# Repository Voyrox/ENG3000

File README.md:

# ENGG3000 Group 1

ESP32 ultrasonic sensor nodes that detect boats and report readings to a web dashboard.

## Architecture

```
ESP32 ── Wi-Fi ──▶ gateway/server ── TCP :3000 ──▶ Python Server
                                      └── WebSocket:8765 ──▶ Browser
                                    │
                                    └── REST:5000 ──▶ /api/nodes
```

### ESP32 → Server (TCP)

Each ESP32 is a servo scanner (`src/Scanner.cpp`; every pin and setting is in `src/Config.h`): two ultrasonic sensors side by side (left: echo/trigger on GPIO 13/12, right: GPIO 27/26) on a servo (GPIO 33) that turns towards whichever sensor sees the player, plus the dead-zone buzzer (GPIO 32). Every signal is on the board's VIN-to-EN header; the sensors' 3V3 is on the other one. Nodes scan one at a time: the server hands out turns (`TURN` / `HALT`) so their pings never overlap. It connects to the laptop hotspot, opens a persistent TCP socket on port `3000`, receives a numeric node ID, and sends a JSON line after every scan step:

```json
{"nodeId":1,"mac":"14:08:08:AB:F6:20","avg":82.40,"left":81.90,"right":82.90,"angle":112,"scanState":0}
```

- `avg` is the node's distance to the player (cm): the mean of the ultrasonics reading inside the scan range, or the nearer real echo if neither is; `-1` when neither heard anything
- `left` / `right` are the two ultrasonics (cm), `-1` for no echo
- `angle` is the servo angle the pair was read at: 90 points straight out into the play area, larger turns towards screen-left
- `scanState` is `0` found (both readings agree), `1` half-found (one sees the player), `2` lost (sweeping)

The server sends control lines back: `SYNC <tick>`, `TURN` / `HALT`, `ROLE LEFT` / `ROLE RIGHT` once the game's calibration screen has identified the node (again whenever it reconnects), which sets that mount's servo limits, and `AIM 90` / `SCAN` while the calibration screen is open / after it closes, `PULSES <n>` (multi-pulse, below), `LOOK <deg>` (handover, below), and `FARHOLD <0|1>` / `FARSTEER <0|1>` (far hold and far steer, below). A node boots holding its servo at 90 and sweeps only once told `SCAN`; the server sends `AIM 90` or `SCAN` the moment a node connects, so one that reboots mid-calibration never moves.

**Multi-pulse** is the `PULSES <n>` command: in found or half-found, the node takes `n` pulse pairs at one angle (1 = off, the default; at most 5), averages each sensor's readings with outliers left out, and only then reports one reading and moves. A lost pair still sweeps straight away. "Outliers" means: pulses with no echo are skipped, echoes outside the play area are skipped if any pulse saw the player inside it, then an echo more than `OUTLIER_TOLERANCE_CM` (20 cm) from the median is dropped (for two echoes that disagree, the nearer one is kept), and the rest are averaged. It is switched with the **Pulses** button on the game screen (top right: Off, 2, 3), which sends `{"type": "nodes:pulses", "count": 3}`; the server passes the count on to every node, and again to each node as it connects. With multi-pulse on, a node reports about once every `n` pairs while it has the player, instead of after every pair.

**Far hold and far steer** are two server → node lines, `FARHOLD <0|1>` and `FARSTEER <0|1>` (`src/CommandHandler.cpp`): `1` turns the setting on, `0` off. Far hold: after an echo at least `FAR_RANGE_CM` (100 cm) out, a lost pair keeps the servo where it is, for up to `FAR_HOLD_PAIRS` (3) lost pairs in a row, before the sweep starts. Far steer: a half-found echo that far out steers by `FAR_STEER_STEP_DEG` (1 degree) instead of `STEER_STEP_DEG` (3). Both are on in the firmware until the server says otherwise (`DEFAULT_FAR_HOLD`, `DEFAULT_FAR_STEER` in `src/Config.h`) and on in the server (`nodes_far` in `app.py`), which sends both lines to every node as it connects, and the changed one to every connected node when a switch changes:

```text
FARHOLD 1
FARSTEER 0
```

They are switched with **Far hold** and **Far steer** on the phone control panel (`/control`, `CON=1`, under *Sensors*). Those buttons go straight to the server, so they work with no game page open; `enabled` (boolean) is the new setting, and anything that is not `true` or `false` is ignored:

```json
{"action": "farHold",  "enabled": false}
{"action": "farSteer", "enabled": true}
```

The server answers every control panel with `far:status` (server → control panel), and sends it to each panel as it connects; `hold` and `steer` (booleans) are the two settings as the server holds them, and the panel's buttons show them:

```json
{"type": "far:status", "hold": true, "steer": false}
```

**Handover** (`Website/handover.py`): when one node has seen the player in one place for 5 s, the server aims the other node at them. A node's confidence is the share of its readings in the last 5 s that land inside the play area within 20 cm of their median point; dropped echoes count against it. It is confident at 80% or more, once it has been reporting for 5 s. While one node is confident and the other is not seeing the player there, the server sends the other `LOOK <deg>`, the bearing from it to that point. It is only ever sent while that node does not hold the turn, and is sent again whenever the bearing moves by more than 5 degrees, until the node's own reading agrees (within 30 cm). `LOOK` is not a hold: the node turns there and tracks, steers and sweeps from that angle as usual, after waiting out the swing (`LOOK_SETTLE_MS_PER_DEG`). Every node's confidence, the ± spread of its points and which node it is following go out in `nodes:update` as `confidence`, and the phone control panel shows them in its Sensors table. `HANDOVER=0 python Website/app.py` keeps the confidence but sends no `LOOK`; the control panel's Handover switch (Sensors) does the same while the server runs, and the server tells the panel which it is (`handover:status`). With the empty-room firmware, a node learning the room is never aimed, and one whose room is not learnt yet never counts as confident, because a chair is the steadiest "player" there is.

**Search** (`Website/search.py`, Aaron, 6 Oct): a node that loses the player is first aimed back at the cell they most likely are in, and only sweeps once it has checked there. For a still player the cell is the one both nodes' found and half-found readings put them in most often over the 3 s before the latest of them (each reading's own point: its distance plus the body radius along its servo angle; ties go to the latest); for a moving one, the cell they were walking into (`heading.py`, from the game's `track:update`, when its Tracking detector says they are moving; the Heading switch turns this off). From the node's first lost reading the server sends it `LOOK <deg>`, the bearing to the cell's centre within its servo's limits, and sends it again after each lost reading there, since the firmware sweeps a step after every lost reading; after 3 lost readings at the cell it sends nothing more and the sweep takes over. A found or half-found reading ends it. A node that has given up on a cell only looks again for someone seen after it gave up (Aaron: "after some time it should just give up if not found"); a cell needs 2 readings in the window, so one stray echo never sends it back. After a far echo (100 cm or more, Far hold on) the firmware's far hold goes first and the search starts on the last held reading. With no reading on the board in the last 5 s there is no cell, and a lost node sweeps as before. The search's `LOOK` goes before the handover's, which leaves a node being searched alone. Each node's search goes out in `nodes:update` as `search` (the State column on the control panel says "checking" and the cell, then "sweeping"). `SEARCH=0 python Website/app.py` starts with it off; the control panel's Search switch (Sensors) turns it off and on while the server runs (`search:status`). It needs no new firmware. The game resets it with `round:start` (which restarts the server-side chain too), and `calibration:update` gives it the cells' depths.

#### Firmware layout (`src/`)

| File | What it is |
|------|------------|
| `Config.h` | Every pin, range, timing, step size, servo limit, network setting and multi-pulse setting |
| `main.cpp` | Creates the objects below; `setup()` and `loop()` |
| `UltrasonicSensor.h/.cpp` | `UltrasonicSensor`: one sensor, a distance in cm or `-1` for no echo |
| `ScannerServo.h/.cpp` | `ScannerServo`: the servo angle, per-role limits (`NodeRole`), the calibration hold and settle time |
| `Scanner.h/.cpp` | `Scanner`: the found / half-found / lost state machine and multi-pulse; `ScanReading`, `ScanState` |
| `NodeConnection.h/.cpp` | `NodeConnection`: Wi-Fi, the TCP socket, the handshake and node id, sending and reading lines |
| `ServerDiscovery.h/.cpp` | Finds the server on the local subnet (only with `AUTO_DISCOVER_SERVER`) |
| `CommandHandler.h/.cpp` | `CommandHandler`: carries out the server's control lines |
| `Telemetry.h/.cpp` | The JSON line above |

The Wi-Fi network and server IP default to the values in `Config.h`. To use your own without committing them, add them to your own (gitignored) `platformio.ini`:

```ini
build_flags =
    '-DNODE_WIFI_SSID="MyHotspot"'
    '-DNODE_WIFI_PASSWORD="secret"'
    '-DNODE_SERVER_IP="192.168.137.1"'
```

**Calibration** is the game's sensor-assignment screen: both servos are held still at 90 degrees (`AIM 90`) for the whole screen - through both steps, LEFT then RIGHT - while the operator aims the nodes straight out into the play area by hand and identifies each node with a hand in front of it; each live-readings row shows the angle the node reports, amber if it is not 90; Start Game then lets the nodes scan again (`SCAN`). There is no play-area (corner) calibration: the game plays on the default bounds, rows between 20 and 140 cm in every column. Each game page asks for the hold with `{"type": "nodes:aim", "hold": true}` and releases it with `false`; the servos stay held while any open page is on the calibration screen, so another tab or device on a different screen cannot release them, and a page that closes stops holding.

The game puts each node on the screen edge at the centre of an outer column. How the player is placed is switched on the phone's `/control` page only (Aaron, 5 Oct; the game board draws one cursor and no buttons): **Dynamic** (the default), **Line of sight**, **Trilateration** or **Average**, under *Placing the player*. Picking one of the last three turns Dynamic off. With Dynamic on, its button says which one it is following (e.g. `Dynamic (TRI)`), or which of its rules is placing the player: `FAR` (far priority: both nodes read past 110 cm and agree), `A1` / `A3` (the near node in its far corner), `MID`, `COL L` / `COL R` (the column lock: where the two servo lines cross) or `L` / `R` (a lone confident node); each rule has its own switch under *Dynamic's rules*. **Compare**, beside it, rings where line of sight, trilateration and the average put the player (LOS, TRI, AVG) on the control panel's pad, while the cyan cursor follows the one placing the player (the thick ring). The game's sensor panel lists all three positions. See *Placing the player* under the filtering pipeline. With no `angle` from either node there is no line of sight, and every method is trilateration.

**Out of bounds** appears in one case only: both nodes are lost (Aaron, 5 Oct). Each node's last *n* readings are scored as the control panel shows them - *found* +1, *half* 0, *lost* -1 - and a node whose scores add up to 0 or less is lost, so the odd found reading among lost ones does not stop it, and a node mostly finding the player never is. *n* is 21 by default; set it on the phone control panel under *Out of bounds* (minus and plus), which also shows each node's score now. The game keeps it in that browser, and passes it to the server when `SERVER_FILTERING` is on. Each reading counts once, when it arrives; a node waiting for its turn keeps the readings of its last one, and a node is not lost until it has had *n* readings in the round. A position off the board keeps the player on the edge square, a tenth of a square inside the edge (`EDGE_INSET`), and the game carries on; the sensor panel says `off board: edge`. Unusable readings are ridden out on the last square for as long as they last. If neither node sends anything for 5 s (`tuneSensor({ offlineMs })`), or the server says both are offline, the game says **Sensors offline** instead and the round waits. Waiting for a first position shows no message.

The board is drawn with the row **nearest the screen at the top**, so stepping towards the screen moves the cursor up. Only the drawing is flipped (`boardRow()` in `game.js`, one switch, `NEAR_ROW_AT_TOP`): grid row `gy = 0` is still the row nearest the screen everywhere else, and left/right is unchanged. The phone control panel's touchpad maps onto the board as drawn. A finger on it takes the game's cursor over from whichever mode is running (sensors or mouse) and lifting it hands the cursor straight back; nothing else on the game screen changes (Aaron, 5 Oct). The sensors keep running underneath - the sensor panel, LIVE STATS and LIVE DATA carry on - but while the finger is down they cannot hold the round, put up Out of bounds or Sensors offline, or raise the too-close alert, and only the finger's cursor scores. There is no Remote mode any more: the panel's *Input* row is Sensors and Mouse, and *Start sensor round* replaces *Start remote round*.

### Python Server (Flask + WebSockets)

`app.py` runs three concurrent services:

| Service | Port | Role |
|---------|------|------|
| TCP broker | 3000 | Accepts ESP32 connections, assigns node IDs, reads sensor lines |
| WebSocket | 8765 | Pushes `nodes:update` messages to browser clients |
| Flask (REST) | 5000 | Serves the web UI and `/api/nodes` endpoint |

When the TCP broker receives a sensor reading, it updates the node's state and broadcasts to all connected browsers via WebSocket:

```json
{"type":"nodes:update","nodes":[{"id":1,"address":"192.168.1.42:12345","latest":"{...}","online":true,"rps":2.0}]}
```

Nodes that haven't reported in 5 seconds are marked stale and removed.

With server-side filtering on (`SERVER_FILTERING=1`, see below), the same
message gains two fields; the existing fields do not change. `coordinate` is
`null` until the sensors are assigned and a reading arrives. `predicted_cm`
is each channel's predicted distance in cm (left, centre, right; see
path prediction below), `null` for a channel with no live track:

```json
{"type":"nodes:update","nodes":[...],"coordinate":{"status":"ok","x":25.0,"y":60.0,"gx":0,"gy":1,"rawGx":0,"rawGy":1,"column":0,"held":false,"heldFor":0,"calibrated":false,"raw":[60.0,null,null],"filtered":[60.0,null,null]},"predicted_cm":[60.4,null,null]}
```

With the flag off neither field is present.

### Browser → Server (WebSocket)

`canvas.js` connects to `ws://<host>:8765/browser` and renders live node data on an HTML canvas. It can also send `menu:select` messages back to the server for UI interactions, `nodes:aim` from the calibration screen (above), and `{"type": "nodes:pulses", "count": 1|2|3}` from the game screen's Pulses button (multi-pulse, above; sent when it changes and after a reconnect; any other count is ignored).

The phone control panel (`/control`, `CON=1`) has **Learn room** and **Forget room** under *Empty room*. Each asks first, then sends `{"action": "room", "room": "learn"|"forget"}`, which the server turns into `LEARN` / `FORGET` for every connected node itself, with no game page needed (forgetting also wipes the room from the node's flash). The panel's Sensors table shows each node's room from the `room` field of its readings: none, learning or learnt (`--` for firmware without the room filter).

With server-side filtering on, the server also accepts:

```json
{"type": "sensors:assign",     "slots": [2, 1, 3]}
{"type": "calibration:update", "perColumn": [{"near": 28.5, "far": 140.7}, ...]}
```

`sensors:assign` is sent whatever the flag (the server passes each node its
role), once the hand-wave assignment is complete. `calibration:update` is only
sent when the server reports the flag on (the `coordinate` field in
`nodes:update`) and a corner calibration has been captured - which no screen
does any more, so the server keeps its default bounds. Each is sent again
only if it changes or the socket reconnects, because `sensors:assign` resets
the server's filters. `perColumn` is sent as captured; the server applies the
same shallow-column fallback as `getBounds()`.

The game also passes the control panel's filter switches on to the server,
so the server's chain filters the way the game does. Each goes browser →
server (`syncServerFilterSetup()` in `canvas.js`), only while the server
reports the flag on, whenever the switch changes, and again after the socket
reconnects (a restarted server has forgotten them):

```json
{"type": "filter:kalman",         "on": false}
{"type": "filter:deadZone",       "on": true}
{"type": "filter:cellDecision",   "on": true}
{"type": "filter:trackMoving",    "on": true}
{"type": "filter:cellConfidence", "on": false}
{"type": "sensor:farHalf",        "on": true}
{"type": "sensor:dynamicRules",   "rules": {"farPriority": true, "confidenceNode": true, "columnLock": false, "loneNode": true, "cornerNode": true}}
```

The control panel never sends these itself. Its button sends
`{"action": "<action>", "enabled": true|false}` to the server, which relays it
to every game page as `remote:command`; the game sets its own switch and then
sends the message above. Dynamic's rule buttons send
`{"action": "dynamicRules", "rules": {"<switch>": true|false}}`, only the
switch pressed; the game's `sensor:dynamicRules` carries all five. The server
applies each one to its chain (`apply_filter_event()` in `app.py`, the setters
in `serverFilter.py`); a message without its field is ignored, and so is a
`sensor:dynamicRules` with an unknown switch or a value that is not `true` or
`false`. A `sensor:dynamicRules` changes only the switches it names.

| Message | Field | `/control` switch (section) | Panel `action` | Default | Server side |
|---|---|---|---|---|---|
| `filter:kalman` | `on` (boolean) | Kalman (*Placing the player*) | `kalman` | on | `set_kalman()`, `FilterConfig.kalman` |
| `filter:deadZone` | `on` (boolean) | Dead zone (*Too close*) | `deadZone` | on | `set_dead_zone()`, `FilterConfig.dead_zone` |
| `filter:cellDecision` | `on` (boolean) | Cell decision (*Placing the player*) | `cellDecision` | on | `set_cell_decision()`, `FilterConfig.cell_decision` |
| `filter:trackMoving` | `on` (boolean) | Tracking (*Placing the player*) | `trackMoving` | off | `set_track_moving()`, `FilterConfig.track_moving` |
| `filter:cellConfidence` | `on` (boolean) | Cell confidence (*Placing the player*) | `cellConfidence` | on | `set_cell_confidence()`, `FilterConfig.cell_confidence` |
| `sensor:farHalf` | `on` (boolean) | Far half (*Out of bounds*) | `farHalf` | on | `set_far_half()`, `FilterConfig.far_half` |
| `sensor:dynamicRules` | `rules` (object: `farPriority`, `confidenceNode`, `columnLock`, `loneNode`, `cornerNode`, each boolean) | Far priority, Confidence, Far corners, Column lock, Lone node (*Dynamic's rules*) | `dynamicRules` | all on | `set_dynamic_rules()`, `FilterConfig.far_priority`, `confidence_node`, `column_lock`, `lone_node`, `corner_node` |

What each switches, from the game's `tuning` comments in `game.js` (the
Python copy is the `FilterConfig` field named). **Kalman**: see *Kalman
switch* below. **Dead zone**: on, a node's raw reading is too close when its
point along the servo line is in the 10 cm strip at the front of the grid;
off, the raw reading itself is checked, whatever the angle. **Cell
decision**: on, the cell is decided by the margin, the dwell and each node
against itself; off, by the older majority vote. **Tracking**: while the
player is moving, the cell decision follows them with a shorter dwell.
**Cell confidence**: the cell decision uses how sure the game is that the
player has stood in each cell. **Far half**: a half reading whose own point
is in the back row scores +1 towards Out of bounds, as found does.
**Dynamic's rules**: see *Placing the player* below.

## Filtering pipeline (`Website/filterRules.py`)

The sensor filtering rules - slew gate, median, Kalman, FFT low-pass, dropout
hold, raw-reading proximity alert, column selection, calibrated row mapping, cell majority vote
and hold-and-recovery - are ported from `public/displays/game.js` into a
standalone Python pipeline, so the filtered coordinate can be computed once on
the server instead of in every browser tab.

**It is wired into `app.py` behind a flag, off by default.** Start the server
with `SERVER_FILTERING=1` to run it; without the flag the server and the
browser behave exactly as before and the game filters in `game.js`. With the
flag on, the game's cursor and too-close alert come from the server's
`coordinate` instead. `game.js` still holds the JS copy of the rules and stays
the rule owner until step 6 below.
`Website/serverFilter.py` is the adapter between node messages and the
pipeline.

**Path prediction (#18).** `Website/tracking.py` is a per-sensor
constant-velocity Kalman tracker (distance and velocity). With the flag on,
`serverFilter.py` keeps one tracker per channel, feeds it the same fresh raw
reading that channel's filter gets, and publishes every channel's predicted
distance as `predicted_cm` in `nodes:update`, brought forward to the time of
the latest reading. The predictions are **published only**: the coordinate,
the cell vote and the proximity alert do not read them, and the browser does
not use them yet. (The same tracker class is also the Kalman stage of every
channel's filter - see *Channel smoothing* below - where it runs on the
median's output rather than replacing it.) Tunables, all named constants
in `tracking.py` / `serverFilter.py`: process noise 400 cm/s², measurement
noise 0.91 cm, track dropped after 0.5 s without a reading (or when its node
goes offline), extrapolation capped at 250 ms, extra display lead 0 s until
the end-to-end latency is measured.
Hardening, so one bad reading cannot run away with a track: a NaN or ±inf
reading is missing, like no echo (`app.py` keeps it out of the node's median
window too); the 250 ms lead cap counts from the last accepted reading, so a
run of no-echo readings cannot push a prediction further; and a distance
channel's output is clamped to [0, 400] cm (`DEFAULT_MAX_RANGE_CM`), while a
signed channel (`negative_is_missing` off, e.g. an x coordinate) is not.
`PathPredictor` feeds its trackers raw readings, so it also turns on a spike
gate - a reading whose normalised innovation squared is above 6.63
(`DEFAULT_NIS_GATE`, χ² 99 %, 1 degree of freedom) is dropped, unless 3 gated
readings in a row agree to within 20 cm (`REACQ_READINGS`,
`REACQ_SPREAD_CM`), which restarts the track on the latest (the player really
moved) - and a velocity limit of 300 cm/s (`DEFAULT_V_MAX_CM_S`). Both stay
off in the filtering chain's Kalman stage, for parity with `game.js`'s
`kalmanUpdate()`. Tests are in
`Website/tests/test_tracking.py` and `Website/tests/test_serverFilter.py`.

### Placing the player: Dynamic, line of sight, trilateration, average

The nodes scan one at a time (the server hands out 1 s turns), so the two
are never read at the same moment, and a node that has lost the player keeps
reporting whatever its beam hits while it sweeps. The position methods
(`solvePositions()` in `game.js`, `TwoSensorGeometry(method=...)` here):

- **Dynamic** (`dyn`, the default): first three rules (`dynamicRule()`,
  `TwoSensorGeometry._rule()` here; Aaron, 5 Oct), checked in this order.
  Each has a switch on the control panel, under *Dynamic's rules*
  (`setDynamicRules({ farPriority, cornerNode, columnLock, loneNode })`, kept
  in the browser; Python `FilterConfig(far_priority=..., corner_node=...,
  column_lock=..., lone_node=...)`), and the Dynamic button there says which one is placing
  the player. Far priority (`farPriority`, `far_priority`) comes first:
  - **Far priority** (`Dynamic (FAR)`; Aaron, 6 Oct). Past 110 cm a node
    hears the player rarely and mostly with one head: on the rig on 6 Oct
    two thirds of the readings past 110 cm were half, and most runs of them were a
    single reading, so the far position turned up for a tick or two and the
    no-echo and stray nearer readings in between took it back (and pushed
    the nodes towards Out of bounds). When both nodes have read past
    `farPriorityCm` (110; the node's own distance) in the last `farSeenMs`
    (1.5 s, which covers the other node's turn), found or half, and the two
    readings agree - their distances, plus the body radius, cross inside
    both nodes' beams as each was aimed (with the aim tolerance), on the
    board - the player is at that crossing and is not Out of bounds,
    whatever the readings in between. Two far readings that do not agree
    are not the player and change nothing: on 6 Oct the left node read
    113 cm with its servo at its stop (160°) while the right one read 135 cm
    straight out; pairs like that came up in 230 updates of those logs.
    A node that finds the player nearer than 110 cm twice in a row (both
    heads) ends it at once. With Dynamic off it does nothing. Replaying the
    6 Oct logs (00:46-01:09): it placed the player in 288 of 11,280 updates,
    always in the back half, and 29 fewer were Out of bounds. The parity
    trace has segment 31 for it and a run of Dynamic with it off.
  1. **Far corners** (`Dynamic (A1)` / `(A3)`). A1 and A3, the far-left and
     far-right squares, are far from the opposite node - the back-left square
     is some 156 cm from the right node, at a shallow angle. When the left
     node is confident (rule 3) and its own reading puts the player in A1,
     that reading places them and the right node's readings are left out;
     the same for the right node and A3.
  2. **Column lock** (`Dynamic (MID)`, `(COL L)`, `(COL R)`). Each node's servo
     points where it last found or half-found the player. If both have done
     so in the last 1.5 s, where the two servo lines cross says the column,
     whatever the methods make of the distances:
     - **The centre**: the lines cross in the centre column. x is the
       crossing's, kept 8 cm inside the column so the column hysteresis
       cannot hold the player in the column they came from; y is the
       steadiest method's. Once the lines have crossed in the centre, the
       player stays there for 1 s while both nodes still see them, even if
       the crossing strays outside: standing still in the centre must never
       touch a side column (Aaron).
     - **The sides**: the lines cross at least 20 cm inside the left or
       right column (`sideLockDepthCm`), i.e. x 30 cm or less, or 120 cm or
       more. No hold, and it ends any centre hold. Locking a side column
       wherever the lines crossed in it would have cost the 4 Oct
       walk-centre a quarter of its time in the centre column: the servos
       read 20-30° further in than the player, so the crossing strays into
       a side column now and then.

     (Aaron's first form of the centre, LEFT above 90 and RIGHT below 90,
     holds anywhere between the two nodes, which sit in the middle of the
     outer columns: on the 4 Oct centre run it said centre at L-80 every time
     and at R-80 61 % of the time, because the servos read further in than
     the player - L-80 read 112°, R-80 59.5°. The crossing said centre at
     L-80 0 %, R-80 38 %, and C-40/C-80/C-120 100/100/81 %.)
  3. **Lone node** (`Dynamic (L)` / `(R)`). A node whose last two readings found
     the player (both heads), the latest in the last 1.5 s - so it lasts
     through the other node's 1 s turn - and whose own reading (its distance
     along its servo line) is inside the play area - across the board, and
     between its column's near and far edges - is confident. If only one
     node is, that reading places the player and the other node's readings
     are left out. When both are, the steadiest method places the player.

  `tuneSensor({ centreSeenMs, centreHoldMs, sideLockDepthCm,
  confidentReadings, confidentMs })`, Python `FilterConfig(centre_seen_ms=...,
  centre_hold_ms=..., side_lock_depth_cm=..., confident_readings=...,
  confident_ms=...)`. On the rig on 5 Oct (serial logs 19:23-19:43, replayed
  through `filterRules.py`), while the two servo lines crossed in the centre
  column the cursor was in a side column 7 % of the time before the rules,
  and once in 1,507 readings with them (A1's rule, which comes first). The
  side lock placed 182 of 2,868 readings and the far corners 18. The
  play-area check keeps out what the left node found there turned fully in -
  something 9 cm in front of the screen line - and off the left edge of the
  board. On the 4 Oct centre run the rules take C-120 from 62 % to 99 % in
  its column (column changes 23 to 2) and walk-centre from 86 % to 100 % (15
  to 0); L-80, C-40 and C-80 stay at 100 %; R-80 stays poor (4 % to 0 %): the
  right node reads 59.5° with the player straight in front of it, so the
  lines cross in the centre.

  Otherwise Dynamic follows whichever of the other three has kept the
  player in one square of the board the longest (`dynamicLeader()`,
  `DynamicPicker` here). A method whose square keeps changing - bouncing
  between columns - builds up no time, so it is passed over while another
  holds still. Time in a square counts up to 1 s (`tuneSensor({
  dynamicSteadyMs })`, Python `FilterConfig(dynamic_steady_ms=...)`); past
  that a method is fully steady, and of two fully steady methods line of
  sight wins, then trilateration, then the average. So a method stuck on
  furniture can lead only until line of sight has held its own square for
  1 s. A square is a cell, or off the board (which counts as a square of
  its own); a method with no position is out of the running. Replaying the
  4 Oct centre run (`logs/centre-20261004-154946`) through `filterRules.py`,
  Dynamic changed column least on every spot (C-120: 23 times, against 29-33
  for the others; walk-centre: 22 against 27-32) and kept x in the spot's
  column as often as the best single method, or more (walk-centre 77 %,
  against 61-73 %) - except at R-80, where every method was poor (servo aims
  ~15° off) and Dynamic held steady in the wrong column (4 %, line of sight
  37 % with 24 column changes).
- **Line of sight** (`los`). Each node's reading is a point along
  its line of sight - its distance along its servo angle - with an
  uncertainty that is small along the line (3 cm) and grows across it with
  the distance and with how sure the node is of its aim: 4° when both of its
  sensors see the player (found), 15° when one does (half-found). Those feed a
  2D constant-velocity Kalman filter (`LineOfSightTracker`, `losTrack` in the
  game), one reading at a time as it arrives:
  - a node's reading is used once, when it is new - never again while the
    other node takes its turn;
  - a node that is sweeping (lost) is left out;
  - its aim counts in full only when it is new (the servo moved, or the node
    has just started its turn); while the servo holds still each further
    reading's aim counts less (the k-th repeat 1/(k+1)², about one and a half
    readings' worth in all), so the same small aim error is not counted again
    and again, and the two nodes' distances - counted in full every time -
    pin the player down;
  - a reading far from where the track expects the player is left out
    (a 99.9 % gate), and six of those in a row restart the track there;
  - after 1.5 s with nothing usable there is no position.
- **Trilateration** (`tri`): where the two distance circles cross, using
  each node's latest distance however old. The servo angles only check the
  crossing: it must lie inside both sensors' beams - within 7.5° of where each
  servo points, from the datasheet's beam of under 15° (HC-SR04; the supplied
  RCWL-1601 is a pin-compatible copy) - and each distance must be inside the
  sensors' 2-400 cm range. A crossing outside a beam means one node is looking
  at something else (furniture, as a rule), so it is refused, and the nearer
  node places the player by its own distance along its servo angle, as it
  does when only one node has a reading. `tuneSensor({ triBeamHalfDeg: 10 })`
  widens the beam live; Python: `FilterConfig(tri_beam_half_deg=...)`. With
  the aim tolerance on (below) the check allows 20° more.
- **Average** (`avg`): the midpoint of the two.

The switch is on the phone control panel only (`/control`, server started
with `CON=1`), under *Placing the player*, which shows which method is in
use. Its pad draws Compare's rings (LOS, TRI, AVG) where each method puts the
player, and the sensors' cursor, both also while a finger is on the pad; it
lists each method's (x, y) - the one placing the player, or Dynamic is
following, in bold - and its Sensors table gives each node's servo
angle and scan state (found, half, lost) from the node's latest message. Its
buttons come from the game's status, so a new method appears there by itself.
In the browser console, `tuneSensor({ losAccelCmS2, losBearingFoundDeg,
losBearingHalfDeg })` changes the tracker live; `setPositionMethod("tri")`
switches method. The Python side takes the same through `FilterConfig`
(`los_*`), and with `SERVER_FILTERING` on the switch is sent to the server
(`{"type": "position:method", "method": "los"}`).

In simulation - the real `game.js`, two scanner nodes taking 1 s turns, servos
stepping 3° and sweeping when they lose the player, 15° beams, 2 cm distance
noise, a player walking the board and pausing - over three seeds:

| Method | Median error | 90th percentile | Right cell |
|---|---|---|---|
| Before (main) | 7.0 cm | 24.7 cm | 58 % |
| Line of sight | 6.3 cm | 16.8 cm | 65 % |
| Trilateration | 2.3 cm | 22.8 cm | 63 % |
| Average | 3.8 cm | 19.1 cm | 63 % |

With furniture at (60, 100) cm (`--furniture 60,100`), same turns:

| Method | Median error | 90th percentile | Right cell |
|---|---|---|---|
| Line of sight | 10.6 cm | 58.4 cm | 56 % |
| Trilateration | 3.7 cm | 31.9 cm | 61 % |
| Trilateration, no beam check | 13.0 cm | 40.0 cm | 61 % |
| Average | 7.7 cm | 37.4 cm | 62 % |

Reproduce it with `node Website/tools/simulate_positions.js` (options:
`--turn-ms 1000,250,0` - 0 is both nodes at once - `--furniture 140,125`,
`--seeds`, `--methods`, and `--site` to score another copy of `public/`; the
"Before" row is main at 247006b scored that way).

Trilateration is the most exact while the player stands still and the worst
while they move (a distance a turn old is still right for a still player).
With both nodes read at once, all three are within 2 cm (median). Furniture
inside the play area fools a scanner: it "finds" it exactly as it finds a
player. Trilateration's beam check catches most of that: the crossing of the
furniture's distance with the player's is not where both nodes point. What a
refused crossing falls back to matters as much. Placing the player straight
in front of the nearer node, with no angle, scored worse than no check at all
(median 51.5 cm with furniture), so the fallback takes the node's servo angle.
The 7.5° beam is the datasheet's; the rig's is not measured. Check the real
rig with Compare.

Each channel also starts again when its node comes back after a silence
longer than the hold (350 ms) - the other node's turn, as a rule - so the
median and the gate do not hold the new readings back with where the player
was a turn ago.

### Channel smoothing: median → Kalman → FFT

Every sensor channel, in the game (`conditionSensor()` in `game.js`) and in
its Python copy (`ChannelFilter`), runs the five steps below. Each node's
`filtered_distance` in `app.py` runs steps 2-4 only - median, Kalman, FFT, no
gate and no hold - and is published in `nodes:update` and `/api/nodes`;
nothing in the game reads it.

1. **Slew gate** - a jump no person could make is dropped (unchanged).
2. **Median** of the last 5 readings - kills single-reading spikes.
3. **Kalman** - constant-velocity (`tracking.ConstantVelocityTracker`; the
   game has a line-for-line port, `kalmanUpdate()`): process noise
   400 cm/s², measurement noise 0.91 cm. Its velocity state follows a walking
   player without the lag an average adds.
4. **FFT low-pass** over the last 32 Kalman outputs, cut above 3 Hz, read
   back at the newest reading. The sample rate is measured from the window's
   own timestamps: a node sends about 11-12 readings a second while it has its
   turn, fewer with multi-pulse on, and a window never spans the other node's
   turn (the channel starts again after a silence). The window's
   straight-line trend is taken out first and added back after, and the rest
   is mirrored at the newest end. Without that, the FFT treats the window as
   a loop: the old version (mean removed only, 64 readings, 2 Hz) put a
   player walking at 50 cm/s about 35 cm behind where they were.
5. **Hold** - coasts 350 ms through a dropped echo (unchanged); after that, or
   after a re-lock, the median, Kalman and FFT window all start again.

In simulation (40 noise seeds, 2 cm reading noise, 20 Hz) the chain is within
a few hundredths of a centimetre of the median alone on a standing player and
adds no lag to a steady walk; after a quick step it settles in about 0.16 s,
against 0.11 s for the median alone. The FFT stage is the part to judge on the
rig. In the browser console, `tuneSensor({ fftWindow: 0 })` turns it off and
`tuneSensor({ fftCutoffHz: 2 })` / `tuneSensor({ kalmanSigmaA: 200 })` change
it, from the next reading; the Python side takes the same settings through
`FilterConfig` (`fft_window`, `fft_cutoff_hz`, `kalman_sigma_a_cm_s2`, ...).

**Kalman switch.** The control panel's *Kalman* button (`/control`, needs
`CON=1`) turns both of the game's Kalman filters off and on again:
`tuning.kalman`, `setKalman()`, `FilterConfig.kalman`. Off, each node's
distance goes median → FFT, and line of sight places the player at each new
reading's own point along the node's line of sight, with no gate and nothing
kept from the readings before. It is for testing whether a wrong position comes
from the filters or from the readings. The servos never see it: each node
steers on its own pulse pairs. `app.py`'s per-node `filtered_distance` keeps
its Kalman either way. The parity trace has a run of line of sight and one of
Dynamic with it off.

**Angle limit.** The grid is 150 cm across and 160 cm long, with the nodes at
(25, 0) and (125, 0). At each servo angle a node's line runs a set distance
before it leaves the grid: 160 cm straight down it, 203 cm to the far opposite
corner, and only 32.6 cm towards the near side wall at the servo's limit
(`angleLimitCm()` / `angle_limit_cm()`). A filtered distance further than
that, plus 5 cm (`tuning.angleLimitToleranceCm`), is not a player on the grid:
line of sight does not use the reading, and for Dynamic's rules it counts as
no reading (no found streak, no servo line for the column lock, no lone-node
point). Trilateration ignores the limit, and the average's trilateration half
with it. The control panel's *Angle limit* button turns it off and on again:
`tuning.angleLimit`, `setAngleLimit()`, `FilterConfig.angle_limit`,
`filter:angleLimit` to the server. The parity trace has a run of line of sight
and one of Dynamic with it off.

**Tri aim tolerance.** In the centre test (4 Oct) the left servo reported
about 20° further in than the taped spots needed (112° at L-80, 141° at C-80,
134° at C-120). Trilateration's beam check then refused crossings that were
3 cm from the spot, and the nearer node's own point it used instead was
28 cm off, on the edge of the wrong column. With the aim tolerance on, the
beam check lets a crossing be 20° further off each servo's aim than the beam
(7.5 + 20 = 27.5°, plus the player's half-width to the side); whether a node
is in play still follows the beam alone. Replaying the centre test's 1,441
readings: at C-120 the crossing is used for 64 % of readings instead of 5 %
and the median error falls from 35 to 15 cm, on the two walks from 7 % to
39 %, and the empty room still gets no two-node fix. The control panel's
*Tri aim tolerance* button turns it off and on again:
`tuning.triAimTolerance` / `triAimToleranceDeg`, `setTriAimTolerance()`,
`FilterConfig.tri_aim_tolerance` / `tri_aim_tolerance_deg`,
`filter:triAimTolerance` to the server. The parity trace has a run of
trilateration and one of Dynamic with it off. Reseating the left servo's
horn would remove the offset itself; compare with the switch off then.

The game steps a node's filters only on that node's new readings, not on
every animation frame. On the server a no-echo reading (negative) is skipped
rather than put into the median, and the median takes the upper of the two
middle values, as the game's does. The firmware reports the **settled angle
at which** each pair was measured, before moving the servo. For `app.py`'s
per-node `filtered_distance`, a change of angle resets the median, Kalman and
FFT windows: ranges at different bearings are not samples of the same target.
Its FFT uses the measured sampling interval and runs only when the current
window is approximately uniform (within 20%); otherwise the timestamp-aware
Kalman estimate is published. Both the browser and the optional server
coordinate pipeline also reset the affected channel (including its slew gate)
when the reported angle changes; a missed echo at a new angle cannot project
the old range onto that bearing. Their FFT also takes its rate from the
window's own timestamps, but runs on an uneven window too.

The chain runs **once per new reading**. When one node reports, only its
channel gets a new sample; the other channels are marked not fresh and are
not fed their last reading again, which would fill their median windows with
repeats and add lag. The proximity guard still sees every channel's latest
raw reading.

```text
sample ──► Geometry ──► ProximityGuard (RAW) ──► ChannelFilter per channel
       ──► Geometry.locate ──► PlayArea row ──► CellStabiliser ──► HoldPolicy
       ──► FilteredCoordinate
```

| Class | Responsibility |
|---|---|
| `FilterConfig` | Every tunable, with defaults matching `game.js` |
| `PlayArea` | Calibrated bounds, alert threshold, row mapping with hysteresis |
| `ChannelFilter` | Slew gate → median → Kalman → FFT low-pass → hold, for one channel in cm |
| `ProximityGuard` | Too-close on **raw** readings, confirmed over N frames |
| `Geometry` | Abstract: sensor data in, position out — the swappable part |
| `TwoSensorGeometry` | Today's rig: LEFT and RIGHT scanners, placed by line of sight (`LineOfSightTracker`), trilateration or their average |
| `UltrasonicArrayGeometry` | The earlier three-sensor rig, one column each (replays V1 logs) |
| `CartesianGeometry` | A rig that reports `(x, y)` itself, e.g. the servo scanner |
| `CellStabiliser` | Majority vote over recent cells |
| `HoldPolicy` | Abstract: counts bad readings (the pipeline rides them out until nobody is found) |
| `StreakHold` / `MajorityWindowHold` | The two hold rules (see below) |
| `CoordinatePipeline` | Composes all of the above; one instance per player |

### Tests

```bash
python -m unittest discover -s Website/tests
```

Standard library only. `ParityWithGameJs` replays a reading stream that was
recorded by running the **real `game.js`** headless, and requires identical
output at every step, for both default and calibrated bounds. If you change a
filtering rule in `game.js` before integration, regenerate the recording:

```bash
node Website/tests/generate_parity_trace.js
```

`test_app.py` covers the broker and coordinator in `app.py`: the FFT filter,
node identity and MAC de-duplication, the ESP32 handshake, the median/Kalman/FFT
reading pipeline, the stale-node reaper, the HTTP and `/browser` endpoints, and
the scan-turn arbitration. The sockets are faked and the `while True` workers
are stepped by stubbing `time.sleep`, so it binds no port and finishes in about
a tenth of a second.

### Integrating into `app.py`

Steps 1-5 are done, behind the flag; they are kept here as the record of the
design. Step 6 waits until the team drops the flag, since the flag-off path
still needs the JS copy.

**1. Create one pipeline** at module level, next to the other shared state:

```python
from filterRules import CoordinatePipeline, UltrasonicArrayGeometry, PlayArea

pipeline = CoordinatePipeline(UltrasonicArrayGeometry())  # guard with state_lock
sensor_slots = [None, None, None]                         # node id per L, C, R
```

**2. Get the sensor order and calibration from the browser.** Both currently
live only in the browser: `calibrate.js` works out which node is left, centre
and right by hand-wave, and `callibrate_corners.js` holds the play-area
bounds (captured corners once; now the defaults). Node IDs are assigned in TCP connection order and say nothing about
position, so the server cannot infer either. In `browser_handler()`, beside
the existing `menu:select` case, accept:

```json
{"type": "sensors:assign",     "slots": [2, 1, 3]}
{"type": "calibration:update", "perColumn": [{"near": 28.5, "far": 140.7}, ...]}
```

and apply them with `sensor_slots = event["slots"]` and
`pipeline.set_area(PlayArea.calibrated([(c["near"], c["far"]) for c in ...]))`.
Send both from `canvas.js` whenever assignment or calibration completes.

**3. Feed it RAW distances.** In `update_node()`, after `update_distance()`,
build the three-slot reading and update once per incoming node message:

```python
reading = [raw_distance(nodes.get(node_id)) for node_id in sensor_slots]
result = pipeline.update(reading, time.monotonic() * 1000.0)
```

where `raw_distance()` returns the payload's `distance`/`avg` as a float, and
`None` for a missing node or a negative value. (As built, `serverFilter.py`
also passes a `fresh` mask so only the reporting node's channel is fed; the
snippet above alone would re-feed the other nodes' last readings.) **Do not pass
`node["filtered_distance"]`** — that is already median-, Kalman- and FFT-smoothed, and
filtering it again would add lag and could hide the spikes the proximity alert
depends on.

**4. Broadcast the result.** Add it to the existing `nodes:update` payload, or
send its own message:

```python
json.dumps({"type": "coordinate:update", "coordinate": result.to_dict()})
```

**5. Switch the browser over.** In `canvas.js`, on `coordinate:update`, hand
the result to the game through one exported function, e.g.
`window.setServerCoordinate(message.coordinate)`. (As built, the coordinate
rides on `nodes:update`, and `window.setServerFilteringActive()` switches
`game.js` between its own filters and the server's result. With the flag on,
the game says Sensors offline once neither node has sent anything for 5 s, or
both are offline, because the server only recomputes on a new reading.) In `game.js`, that function
replaces what `updateSensorCursor()` computes today:

- store it as `gameState.sensor`, and drive the cursor from its `gx` / `gy`;
- raise the alert when `c.status === "too-close"`.

The game state lives inside `game.js`'s module scope, which is why this goes
through a function rather than `canvas.js` touching it directly.

**6. Delete the JS copy.** Remove the conditioning, column selection, vote and
hold logic from `game.js`. Keeping both means two sources of truth that will
drift apart.

### Behaviour to decide before integrating

**Hold policy.** Since 5 Oct, `game.js` and `CoordinatePipeline` ride
unusable readings out on the last cell for as long as they last; only nobody
found (out of bounds) ends a hold. The pipeline still counts bad readings with
its `HoldPolicy` (`held_for`), but no longer asks it whether to stop.
`StreakHold` (a *consecutive* streak, the default) and `MajorityWindowHold`
(releases once *most* of the last N readings are bad) keep their
`keep_holding()` for `tools/chain_replay.py` and experiments.

**Call rate.** `game.js` steps a node's filters only when that node's reading
is new (its server stamp, `last_seen`, changed), which is what the server's
`fresh` mask does - `CoordinatePipeline.update()` is called once per reading,
and only the reporting node's channel is fed.

### Supporting the scanning rig

`src/Scanner.cpp` tracks the player with two sensors on a servo. Once it
reports a position, use the existing geometry:

```python
pipeline = CoordinatePipeline(CartesianGeometry())
result = pipeline.update((x_cm, y_cm), now_ms)
```

If it reports angle and distance instead, add a `Geometry` subclass that
converts them to `(x, y)` in `channels()` / `locate()`. Nothing downstream
needs to change.

## Measuring sensor noise

Before changing the hardware, the firmware or the filters, measure. Start the
server with the raw-reading recorder on:

```
REC=1 python Website/app.py
```

Every JSON line a node sends is written, unfiltered, to
`logs/raw-YYYYmmdd-HHMMSS.csv` at the repository root (`/logs` is gitignored;
the MAC is never written). Columns: `t_s` (server receive time from the start),
`label`, `node_id`, `role`, `has_turn`, `ms_since_turn`, `pulses`, `left_cm`,
`right_cm`, `avg_cm`, `angle_deg`, `scan_state`; `-1` is a no echo, and a field
the node did not send is empty.

With both nodes scanning, and the game page closed or at least off the
calibration screen (the calibration hold stops the servos, and multi-pulse does
nothing while they are held), run the bench test. It asks you to put a target
at each distance, for each Pulses setting, and labels those readings
(`p3-60cm`); the time spent moving the target is not labelled:

```
python Website/tools/bench_noise.py capture --distances 30 60 90 120 --pulses 1 3 --seconds 20
python Website/tools/bench_noise.py report logs/raw-YYYYmmdd-HHMMSS.csv
```

The report gives, per step, node and sensor (`left`, `right`, `avg`):

| Column | Meaning |
|--------|---------|
| `n` | readings |
| `no-echo%` | readings with no echo at all |
| `median` / `bias` | the middle reading, and how far it is from the distance in the label |
| `sigma` | 1.4826 x the median absolute deviation: the noise, ignoring outliers |
| `std` | standard deviation: the noise including outliers |
| `outlier%` | echoes more than 10 cm (`--outlier-cm`) from the step's median |
| `found%` | readings where both sensors agreed (`scanState` 0) |

A second table shows, per node, readings received without the scan turn, and
the outlier and no-echo rates in the first 150 ms after the node was given the
turn against the rest: if the early rate is clearly worse, the two nodes are
hearing each other at the hand-over. `--csv FILE` also writes the first table
out.

The bench test sets Pulses itself through `POST /api/pulses`
(`{"count": 1|2|3}`) and the labels through `POST /api/recording/label`
(`{"label": "..."}`, 404 when the server is not recording), and turns Pulses
back off at the end.

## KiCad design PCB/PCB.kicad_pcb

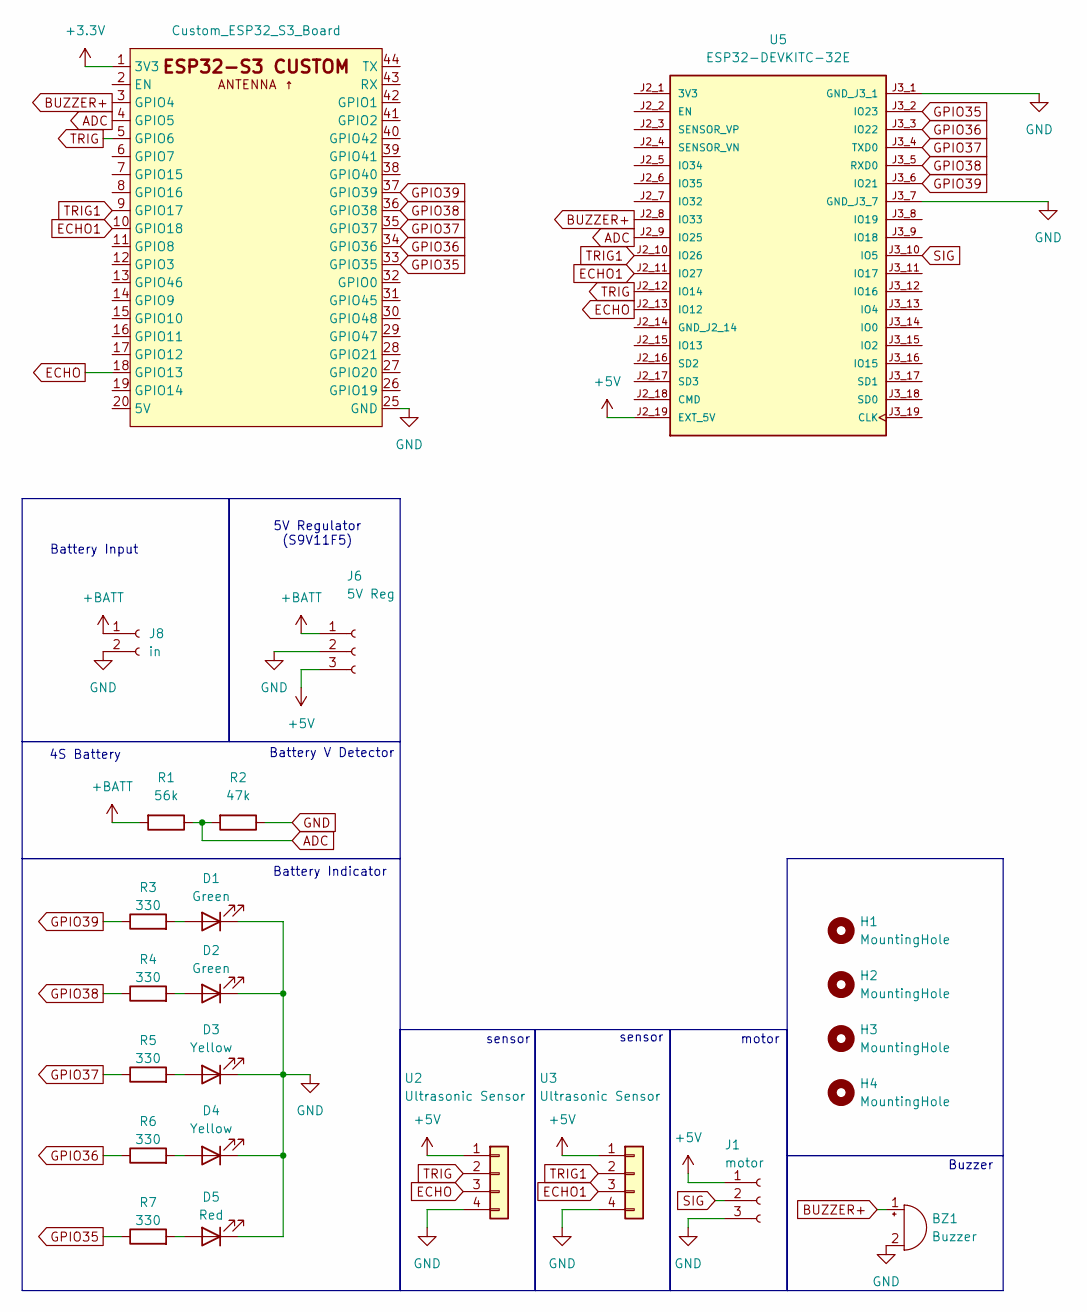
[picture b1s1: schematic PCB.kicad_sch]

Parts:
BZ1: Buzzer; Buzzer_TDK_PS1240P02BT_D12.2mm_H6.5mm
D1, D2: Green; LED_D5.0mm
D3, D4: Yellow; LED_D5.0mm
D5: Red; LED_D5.0mm
H1, H2, H3, H4: MountingHole; MountingHole_2.2mm_M2_DIN965
J1: motor; PinHeader_1x03_P2.54mm_Vertical
J6: 5V Reg; PinHeader_1x03_P2.54mm_Vertical
J8: in; PinHeader_1x02_P2.54mm_Vertical
R1: 56k; R_Axial_DIN0207_L6.3mm_D2.5mm_P7.62mm_Horizontal
R2: 47k; R_Axial_DIN0207_L6.3mm_D2.5mm_P7.62mm_Horizontal
R3, R4, R5, R6, R7: 330; R_Axial_DIN0207_L6.3mm_D2.5mm_P7.62mm_Horizontal
U2, U3: Ultrasonic Sensor; PinHeader_1x04_P2.54mm_Vertical
U4: Custom_ESP32_S3_Board; ESP32-S3-DevKitC
U5: ESP32-DEVKITC-32E; MODULE_ESP32-DEVKITC-32E; PARTREV 1.4

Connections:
+5V: J1.1, J6.3, U2.1, U3.1, U5.J2_19 (EXT_5V)
+BATT: J6.1, J8.1, R1.2
ADC: R1.1, R2.2, U4.4 (GPIO5), U5.J2_9 (IO25)
BUZZER+: BZ1.1 (+), U4.3 (GPIO4), U5.J2_8 (IO33)
ECHO: U2.3, U4.18 (GPIO13), U5.J2_13 (IO12)
ECHO1: U3.3, U4.10 (GPIO18), U5.J2_11 (IO27)
GND: BZ1.2 (-), D1.1 (K), D2.1 (K), D3.1 (K), D4.1 (K), D5.1 (K), J1.3, J6.2, J8.2, R2.1, U2.4, U3.4, U4.25 (GND), U5.J3_1 (GND_J3_1), U5.J3_7 (GND_J3_7)
GPIO35: R7.1, U4.33 (GPIO35), U5.J3_2 (IO23)
GPIO36: R6.1, U4.34 (GPIO36), U5.J3_3 (IO22)
GPIO37: R5.1, U4.35 (GPIO37), U5.J3_4 (TXD0)
GPIO38: R4.1, U4.36 (GPIO38), U5.J3_5 (RXD0)
GPIO39: R3.1, U4.37 (GPIO39), U5.J3_6 (IO21)
unnamed: D1.2 (A), R3.2
unnamed: D2.2 (A), R4.2
unnamed: D3.2 (A), R5.2
unnamed: D4.2 (A), R6.2
unnamed: D5.2 (A), R7.2
SIG: J1.2, U5.J3_10 (IO5)
TRIG: U2.2, U4.5 (GPIO6), U5.J2_12 (IO14)
TRIG1: U3.2, U4.9 (GPIO17), U5.J2_10 (IO26)

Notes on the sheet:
Battery Input
Buzzer
Battery Indicator
4S Battery
5V Regulator (S9V11F5)
Battery V Detector
motor
sensor

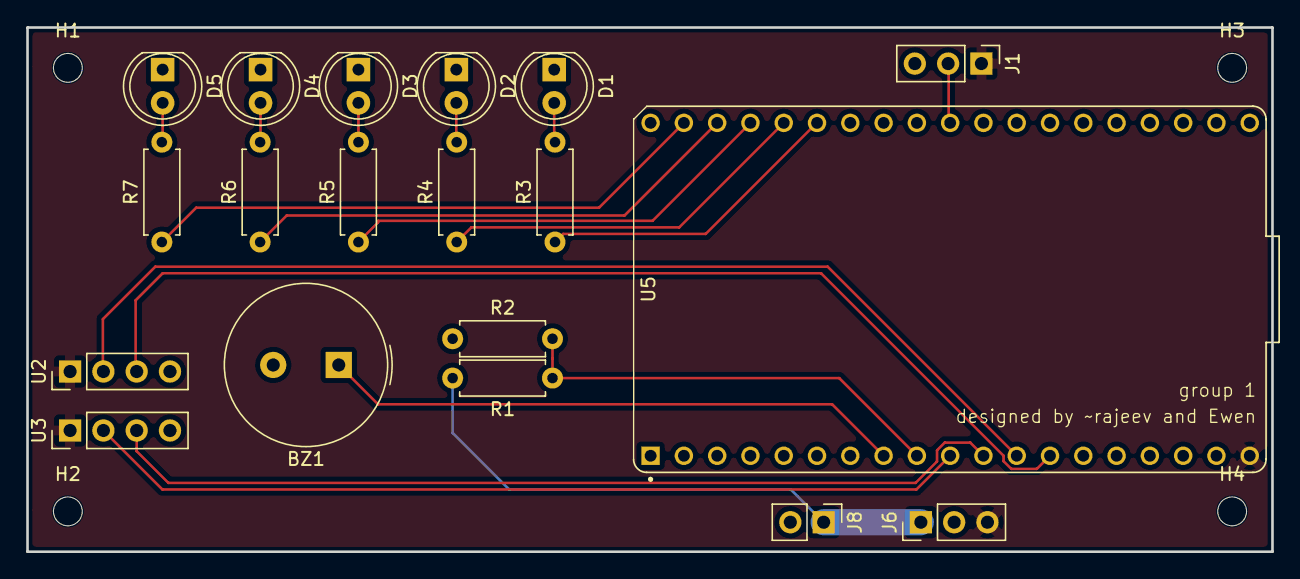
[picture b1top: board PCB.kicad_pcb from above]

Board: 2 copper layers, 95.0 x 40.0 mm, 23 parts (0 on the bottom side), 20 nets.
